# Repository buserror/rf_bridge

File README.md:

# Home Automation: MQTT <-> RF 433Mhz Bridge for switches and sensors.
This project implements a RF bridge for 433Mhz devices. The idea is to have a small AVR do the mod/demod and send diggested messages on it's serial port to a linux box for processing; in this case bridging sensors and switches to a MQTT broker.

This was made to interface my cheap RF433 gizmoz (wall switches, outlets, temperature sensors etc) to the home automation, and ultimately the Amazon echo/Alexa.

The fact the AVR does all the sensitive bits means the linux program doesn't eat a lot of CPU and can concentrate on the applicative parts, which is the MQTT bridging.

<p align="center">

<p align="center">Finished Project (Minus case)</p>
</p>

## The AVR Bits
The firmware can run on anything with about 2KB of SRAM (currently uses <1300 bytes), and a clock of 16Mhz. The firmware 'samples' the RF signal from the 433 module at about 64khz and tries to detect edges, then regular pulses, then does some decoding until a 'long low pulse', and forwards it on.

The firmware can also transmit (altho this part isn't finished, only ASK is working for now) using the same message format. The code doesn't try to be too clever and has a 'raw' mode it can be switches into to forward raw pulses straight to the host for analysis. 

The firmware is capable of decoding both Amplitude-Shift Keying (ASK) and manchester encoding. It's completely frequency/pattern independent and continuously search for signal in the noise before applying some filtering and hopefully forward the whole diggested message onward.

Also, I wanted to publish a firmware that looks marketedly different from the typical arduidiot[0] firmware that is all bloaty, synchronous and so on. This firmware uses coroutines, is completely asynchronous and allows the AVR to be in sleep mode most of the time. *This* is he way I do embedded; use a tick clock of any frequency (here, I use the sampling clock) and derivate everything else from it, and sleep in between ticks when you no longer need the CPU.

The only bit that is not synchronous to that tick mark is the UART, it's all interrupt driven, and it's nicely isolated using biggish FIFOs so it's unlikely to become blocking.

[0]: Arduidiot is my name for the well known boards. Since a few years back when they started suing each others for the name, I decided my version of the name was a lot more appropriate.

### Message format
A Typical message will be sent to the host like this, for a dumb switch:

    MA:40553300#19!3f*36

This is a message that already has been decoded as ASK encoding, has 0x19 bits, the clock duration was 0x2f timer clock cycle per bit, and the checksum was 0x36.

A more involved message would be:

    MM:0028b4206b0b38c0#40!3f*ff

This one has 'M'anchester encoding, 0x40 bits with 0x3f/2 timer ticks per bits.

The reason the timer clock is returned is to be able to reply the message back. Currently you can 'replay' ASK messages by just sending them back to the serial port. They will be replayed 3 times.

## The Linux Bits
The linux bit sits on the serial port, reads diggested messages and 'maps' them to MQTT messages. For dumb on/off switches it uses a file containing the mapping; but there is an extra decoder for the temperature/humidity sensor. The mapping is'nt terribly clever and use a flat file. 

The linux process uses libmosquitto to connect to a MQTT broker. I might try to do away with the libmosquitto requirement, as I don't think I need all the features (and footprint) it brings. I just need a unsecured connection to a broker, and let the broker be 'clever' and do encryption bridging if needs be.

The linux bit also subscribes to the mapped messages, and when it received a MQTT notification that hasn't been sent by itself, it just passes it on to the AVR board for transmisssions. That means you can have a Dashboard with switches, or use Amazon Alexa etc to send the messages on the RF link. No need for a web interface etc, just use MQTT. I personally use Node-Red to do the Alexa Logic bits.

The program can run on pretty much anything, it uses very very little resources, so a Raspberi Pi or anything else will work just fine!

## The Hardware Bits
Note: The hardware has [it's own page](kicad/README.md).

For prototyping I used an Arduino Mega and a RF433 receiver + transmitter. I ended up using 2 antennas separated by about 20cm on the prototype, it works, even if the receiver is a bit overwelmed for a little while after I transmit anything. It otherwises requires no extra hardware. The only thing I did was add a 100R resistor in series with the receiver output, as I was seeing a lot of ringing on the oscilloscope.

The 'real' hardware will be an Arduino nano v3.0 with an Atmega 328p. Powered via the USB port. I've designed a board using Kicad already, and the PCBs are on the way. https://oshpark.com/shared_projects/ZqEOBR2t
Hardware uses a NXP RF switch for sharing an antenna in half-duplex, and apart from a bit of filtering that's about it! More later.

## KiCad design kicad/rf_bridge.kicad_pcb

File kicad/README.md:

#Hardware: rf_bridge

Version 1.x of the hardware uses very little hardware. You need:

  * An Arduino with ~1.5KB SRAM and bout 6KB flash, and runs at least at 16Mhz.
  * A cheap 433Mhz receiver module
  * A cheap 433Mhz transmitter module

The pcb also has a RF switch to be able to share the antenna. The prototype didn't have that and used 2 17cm pieces of wire, and it worked just fine, so it's not *stricly* needed. The hardware here is made to be a neater small package with pigtail connector to a 'proper' antenna.

<p align="center">

<p align="center">Finished Project</p>
</p>
The PCB is very simple, the arduino I picked is a Nano, and it's mounted vertically with the 433 bits, so the result is quite compact.
<p align="center">

<p align="center">Note the 90 Header is offset by <b>one pin</b>.</p>
</p>

  * You can find the schematic as a [.PDF in this directory](rf_bridge_schematics.pdf). 
  * The PCB was ordered from OSHPark ($9 for 3) -- You can order PCBs directly from [this link](https://oshpark.com/shared_projects/YTztWeXs).

##The BOM:

|Ref.|Value|Description
|----|-------|-----------------------|
|C1,C2,C3,
C4,C7|10nF|0603 Caps.|
|C5|100nF|0604 Cap|
|C6|4.7uF|0805 Capacitor (Optional)|
|C8|10pF|0603 Cap (Optional)|
|P1|Nano|[Arduino Nano v3.0](https://www.amazon.co.uk/gp/product/B015MGHH6Q). Use 90 headers for mounting. Only use a 8 pins section of them, and the headers are NOT soldered from the first pin, but from the pin marked GND on the Nano, *NOT the VIN pin*.|
|P2|RF_TX|Both the TX and the RX comes from eBay.|
|P3,P4|RF_RX|[These](http://www.ebay.co.uk/itm/331805856615) are the exact modules I used|
|P5|U.FR|SMT 'pigtail' antenna Connector [Hirose U.FL](http://uk.farnell.com/hirose-hrs/u-fl-r-smt-1-10/rf-coaxial-u-fl-straight-jack/dp/1688077)|
|R1|10K|0603 Pulldown|
|R2|100|0603 Filtering, use anytime you like here even R0|
|U1|SA630|SOIC8. RF Antenna Switcher. [NXP SA630D](http://uk.farnell.com/nxp/sa630d-01-112/rf-switch-spdt-dc-1ghz-soic-8/dp/2400605) |

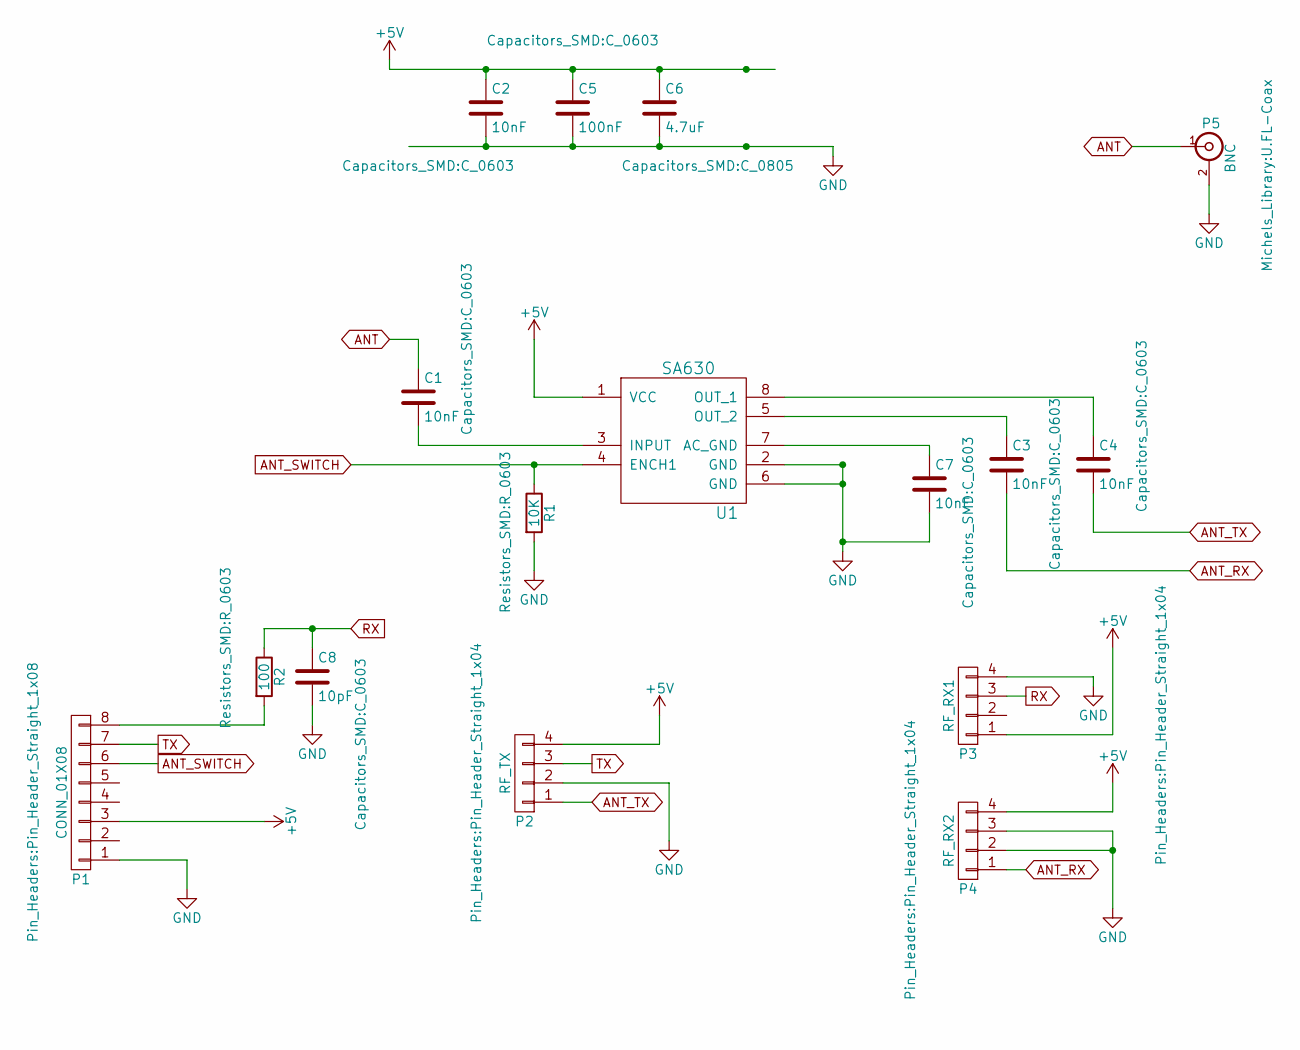
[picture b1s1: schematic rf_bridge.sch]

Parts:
C1, C2, C3, C4, C7: 10nF; C_0603
C5: 100nF; C_0603
C6: 4.7uF; C_0805
C8: 10pF; C_0603
P1: CONN_01X08; Pin_Header_Straight_1x08
P2: RF_TX; Pin_Header_Straight_1x04
P3: RF_RX1; Pin_Header_Straight_1x04
P4: RF_RX2; Pin_Header_Straight_1x04
P5: BNC; U.FL-Coax
R1: 10K; R_0603
R2: 100; R_0603
U1: SA630; SOIC-8-N

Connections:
+5V: C2.1, C5.1, C6.1, P1.3, P2.4, P3.1, P4.4, U1.1 (VCC)
ANT: C1.1, P5.1 (In)
ANT_RX: C3.2, P4.1
ANT_SWITCH: P1.6, R1.1, U1.4 (ENCH1)
ANT_TX: C4.2, P2.1
GND: C2.2, C5.2, C6.2, C7.2, C8.2, P1.1, P2.2, P3.4, P4.2, P4.3, P5.2 (Ext), R1.2, U1.2 (GND), U1.6 (GND)
unnamed: C1.2, U1.3 (INPUT)
unnamed: C3.1, U1.5 (OUT_2)
unnamed: C4.1, U1.8 (OUT_1)
unnamed: C7.1, U1.7 (AC_GND)
unnamed: P1.8, R2.2
RX: C8.1, P3.3, R2.1
TX: P1.7, P2.3

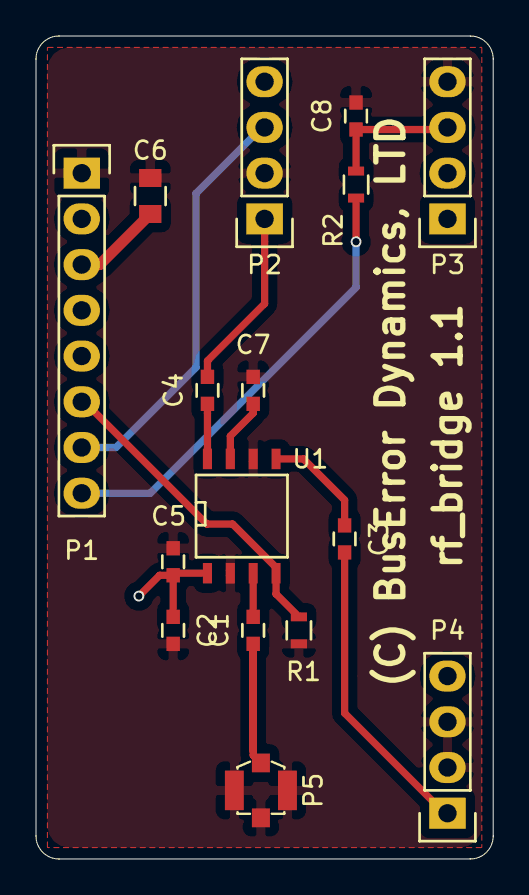
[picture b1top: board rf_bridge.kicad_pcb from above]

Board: 2 copper layers, 25.4 x 45.7 mm, 16 parts (0 on the bottom side), 13 nets.

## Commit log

2017-02-04 Initial commit
    Initial commit.
2017-02-05 Renamed m2560 firmware to match 328p one
    Removed the '433'
2017-02-05 Makefile tweaks
    Mostly simplified some
2017-02-05 Embedded firmware update
    + Replaced the command/message parser.
    + Changed the message format a bit, now uses '#' for bitcounts. This
    allow the aprser to look for a character prefix any any place and know
    what's behind it.
    + Added some debug code to dump the coroutine stack usage data, tweaked
    the stack values accordingly.
2017-02-05 Updated linux code
    Updated to match the firmware new message format. Shoudln't change much
    from now on.
2017-02-06 Prep loader for the message matching table, in progress
    Non functional for now.
2017-02-15 More massaging of the linux bits
    Loads the match file now...
2017-02-15 Tweaks for the linux bits
    Temporary
2017-02-15 Littel tweaks to the AVR firmware
    Bit less stack in use.
2017-02-15 Rewrote message parser, use the structure...
    Ongoing rework on that bit.
2017-02-15 Reworked linux parser, again
    Getting there. parser now parametric, loaded message file uses it.
2017-02-15 Working message matcher for MQTT
    Easy bit, once all the other easy bits are in place..
2017-02-15 Minor updates. Added simavr bits
    Got sidetracked on simavr
2017-02-15 Transmitter work, mostly
    MQTT substriction parsing and stuff, and now debugging the RF433
    transmitter code.
2017-02-15 linux: Added the transmit code
    Temporarily open the output, send the message that requires it, and
    closes it. Allows the port to be used to send commands from a shell
    prompt.
2017-02-15 avr: Fully working transmitter, validated with simavr
    Whoohoo. Etc.
    Added some test code for simavr, validated the bit patterns, programmed
    the chip and p00f it worked. Borderline boring.
2017-02-17 Added a small delay between messages
    Also updated the message table, it's all working now.
2017-02-17 Added traces for simavr
    No functional changes
2017-02-19 Add kicad project for the PCB for the 'final' assembly.
    Designed the carrier board for the final project, and shipped it to
    oshpark...
    First project ever with Kicad, to replace my old trusted Eagle.
2017-02-19 Tweaks for simavr
    Stops simulation when transmitting is done...
2017-02-21 Small update, fixed the kicad project, tweaked comments
    Bit of polishing up. Also added a .pdf of the schematic for reference.
2017-02-22 linux: don't feedback loop the messages we get from the rf
    ... mark bit patterns are they are received from RF, so they don't get
    re-transmitted too soon.
2017-02-22 Pre work on the PIR sensor detect
    The PIR sensor I've sources don't send equal pulses at the start of
    their manchester phrases..So I need to adapt the scanning code for that.
    Captured a trace for this, and started to tweak the scanning code to
    adap to this.
2017-02-23 Added an VCD output trace for validation
    Output of simavr. This shows the firmware starting up, sending a
    message, the *OK and terminating.
2017-02-27 Did a bit of rework on the linux code...
    Also added some install bits and debian 'cheat' package building
2017-03-01 pcb: A few tweaks for next version
    Changed the footprint of the 10nF's to 0603, as I've discovered I have a
    bout 1Kg of them.
    Also changed pinout! Silly me, I used A6 and A7 pins on the arduidiot,
    but these are ADC only, no digital logic. So luckily I had hooked up two
    'spare' pins, so I switched to these instead.
    Also, the rest of the PCB has beem tested, and the switch is defaulting
2017-03-02 avr_cr: Don't use naked attribute
    Turns out it generates bad code
2017-03-02 avr: Now use two timers
    Turns out it takes a lot less cycles to split the job between the two
    comparators, running at the same frequency.
    Since they don't run together, they do less tests.
    Also remove edge detection filtering, turns out nice noisy pulses are
    easy to filter out beforehand before storing them.
    And various other bits
2017-03-03 Increased the maximum ticks per phase
    And tweaked the sync code. Turns out the PIR sensor send their stream
    with very low bitrate, and the pulses were longer than the maximum 127
    that normally tells us it's an end of message. Doh.
2017-03-05 avr: Quite a few changes to handle slow bitrate PIRs
    The PIR sensors are so slow they were overflowing the 7 bits I used for
    pulsecount. So now I use the full 8 bits, and I also tweaked the scanner
    to handle pulse train that don't start with 6-8 identical pulses.
    Also, resized stacks, they are now smaller since we don't one big IRQ,
    but two smaller ones.
2017-03-05 linux: Minor tweaks
    A bit longer delay between pulses
2017-03-05 Added quite a few more VCD input test files
    Easy to capture with sigrock now! Just rename the signal as 'iobH_5' to
    hook it to PORTH5, and use the new simavr -i <input> support for VCD.
    The beauty is that the signal is also in the output VCD.
2017-03-05 Added some docs for the hardware, updated readme
    Added some pics too.
2017-03-05 Readme: Added link to RF modules
    From ebay http://www.ebay.co.uk/itm/331805856615
2017-03-05 Also added a link to the ardiodiots
    On amazon; 14 quid for 5!
2017-03-06 Some more scanner tweaks
    Check manchester header's for some consistency before printing
2017-03-08 Added OOK decoding
    For the PIR's
2017-03-08 Disable libmosquitto if it's too old
    On ubugtu
2017-03-08 Bit of work on a backward scanner
    Trying to simply the scanning logic by starting from the end
2017-03-09 Completely changed scanner/decoders
    Instead of trying to do it on the fly, I now wait until i receive a long
    low pulse for 'end of message' and walk my way backward to the
    beginning, then call the decoder with all the pulses already there.
    That has simplified the code quite a bit, and I removed the decoder
    coroutines that weren't needed anymore
2017-03-13 Prelim work to make an histogram in the scanner
    Will see if I can make 'signature' per protocol..
2017-03-13 Some more tweaks on the signature code
    Getting there...?
2017-03-13 Hmm can't seem to fins a pattern that work for all signal..
    Let's park this.
2017-03-13 linux: Made mqtt optional on command line
    Also, started to change the confg file format
2017-03-14 linux: Big rework of config
    Sections, and so on.
2017-03-16 Revamped config file format
    Now have sections for mqtt, sensors, switches and PIRs (TODO)
2017-03-16 Fixed a problem opening serial on some ports
    Needs clocal on some usb<->serial ports.
2017-03-17 Unified licence in files
    Cleaning up
2017-03-17 Working PIR code now
    Including masking.
2017-03-19 Tweak PIR timeouts; also renamed rf_bridged to rfbridged
    the underscore was confusing debian packages. Also aligned deb version
2017-03-20 Added a small random delay between transmit messages
    255 was not enough, added a small pseudo random extra. This helps with
    messages being transmitted after one another
2017-03-20 Updated version number
    1.0b4. Quite stable too, nearing a 1.0
2017-05-11 Reworking the reader/writer code
    Will implement a send queue for handling resends, and to handle waiting
    for 'silence' before attemping to send.
2017-07-06 New version, in progress
    Handling the multithreaded queuing of messages
2017-07-07 Added the resend logic
    Needs testing
2018-01-16 Fixed some warnings.
    asprintfs etc.
